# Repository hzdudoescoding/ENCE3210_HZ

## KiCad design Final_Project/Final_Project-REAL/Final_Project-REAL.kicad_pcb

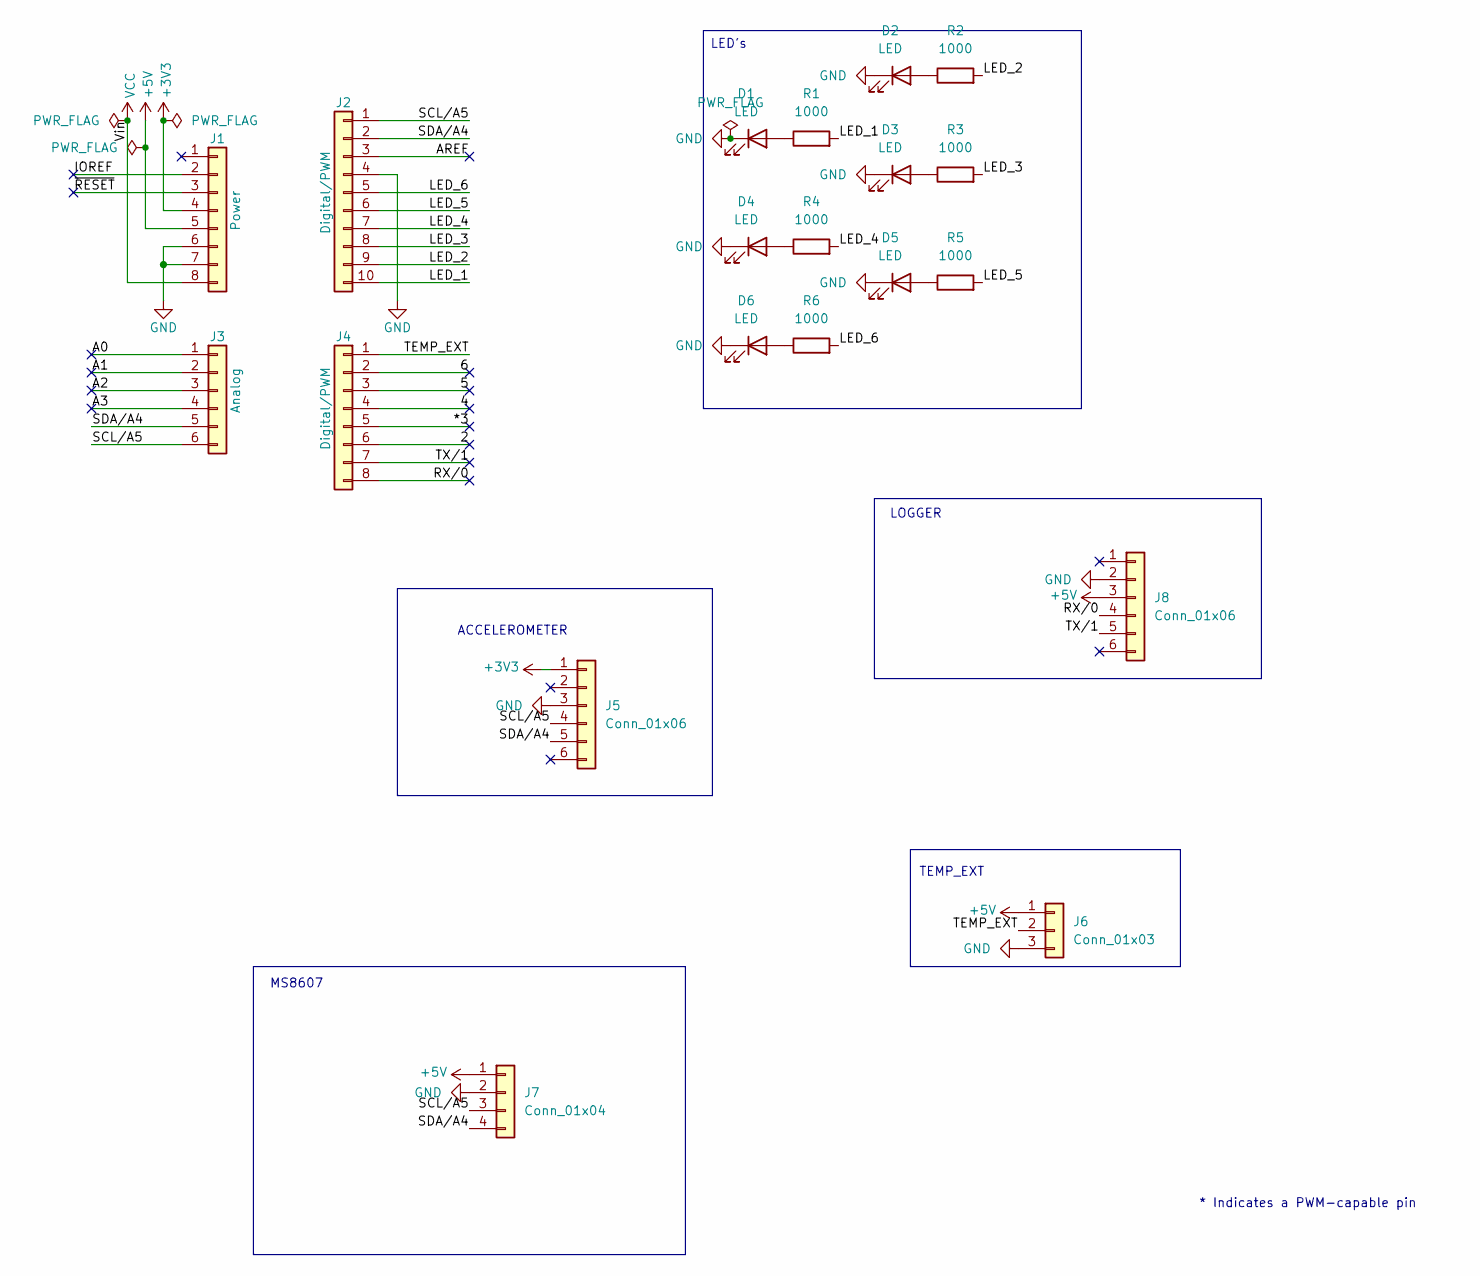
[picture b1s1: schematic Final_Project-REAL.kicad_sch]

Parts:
D1, D2, D3, D4, D5, D6: LED; LED_D5.0mm
J1: Power; PinSocket_1x08_P2.54mm_Vertical
J2: Digital/PWM; PinSocket_1x10_P2.54mm_Vertical
J3: Analog; PinSocket_1x06_P2.54mm_Vertical
J4: Digital/PWM; PinSocket_1x08_P2.54mm_Vertical
J5, J8: Conn_01x06; PinSocket_1x06_P2.54mm_Vertical
J6: Conn_01x03; JST_XH_B3B-XH-A_1x03_P2.50mm_Vertical
J7: Conn_01x04; PinSocket_1x04_P2.54mm_Vertical
R1, R2, R3, R4, R5, R6: 1000; R_Axial_DIN0207_L6.3mm_D2.5mm_P10.16mm_Horizontal

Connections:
+3V3: J1.4, J5.1
+5V: J1.5, J6.1, J7.1, J8.3
/2: J4.6
/4: J4.4
/5: J4.3
/6: J4.2
/*3: J4.5
/A0: J3.1
/A1: J3.2
/A2: J3.3
/A3: J3.4
/AREF: J2.3
/IOREF: J1.2
/LED_1: J2.10, R1.2
/LED_2: J2.9, R2.2
/LED_3: J2.8, R3.2
/LED_4: J2.7, R4.2
/LED_5: J2.6, R5.2
/LED_6: J2.5, R6.2
/RX/0: J4.8, J8.4
/SCL/A5: J2.1, J3.6, J5.4, J7.3
/SDA/A4: J2.2, J3.5, J5.5, J7.4
/TEMP_EXT: J4.1, J6.2
/TX/1: J4.7, J8.5
/~RESET: J1.3
GND: D1.1 (K), D2.1 (K), D3.1 (K), D4.1 (K), D5.1 (K), D6.1 (K), J1.6, J1.7, J2.4, J5.3, J6.3, J7.2, J8.2
unnamed: D1.2 (A), R1.1
unnamed: D2.2 (A), R2.1
unnamed: D3.2 (A), R3.1
unnamed: D4.2 (A), R4.1
unnamed: D5.2 (A), R5.1
unnamed: D6.2 (A), R6.1
VCC: J1.8

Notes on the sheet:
TEMP_EXT
MS8607
* Indicates a PWM-capable pin
LED's
LOGGER
ACCELEROMETER

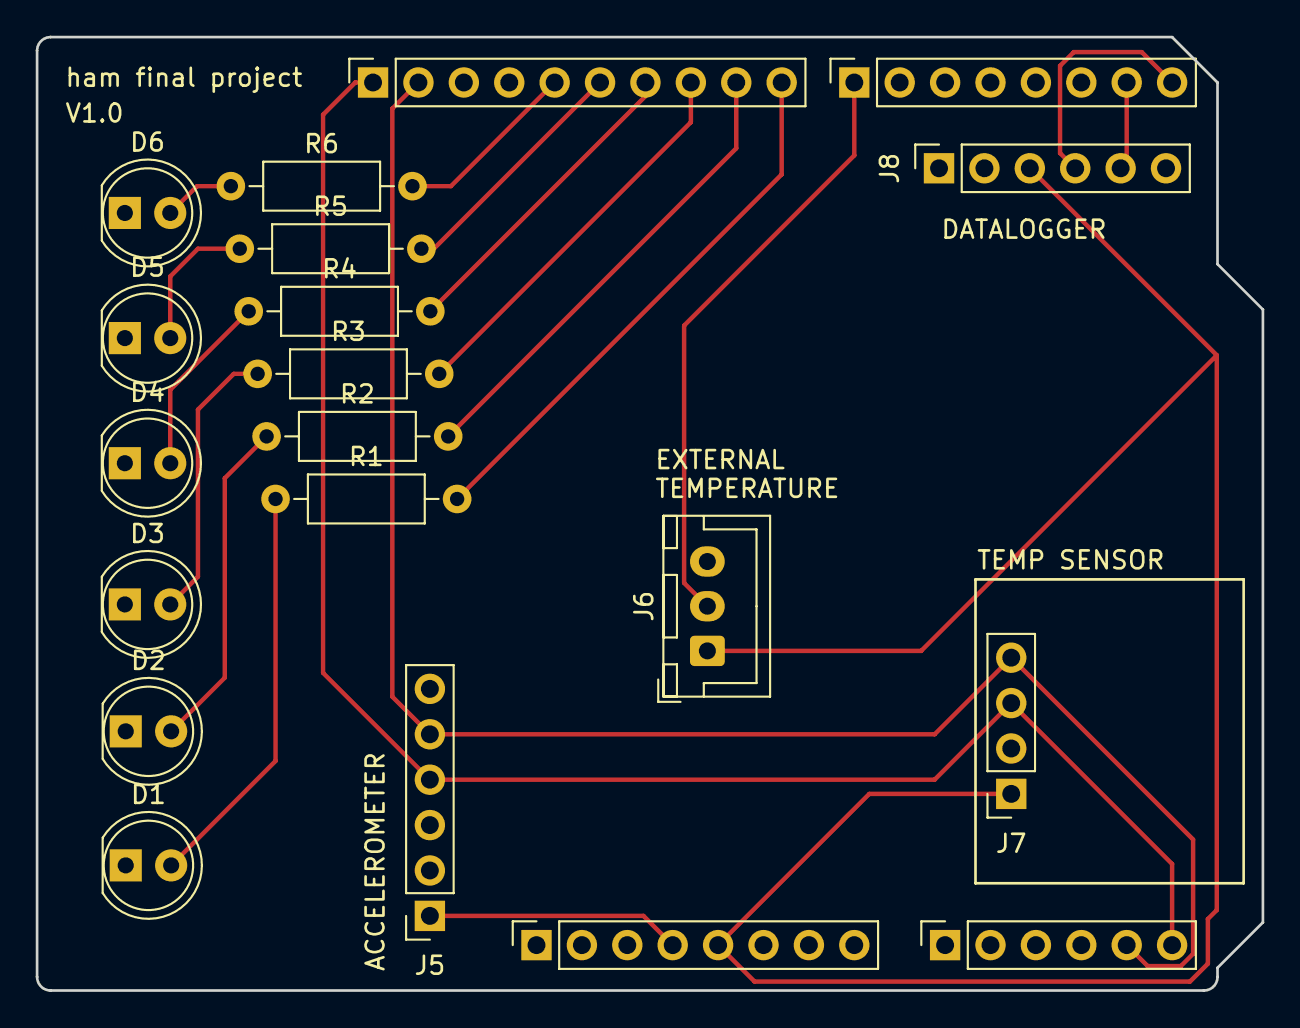
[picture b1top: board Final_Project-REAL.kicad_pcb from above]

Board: 2 copper layers, 68.6 x 53.3 mm, 20 parts (0 on the bottom side), 20 nets.

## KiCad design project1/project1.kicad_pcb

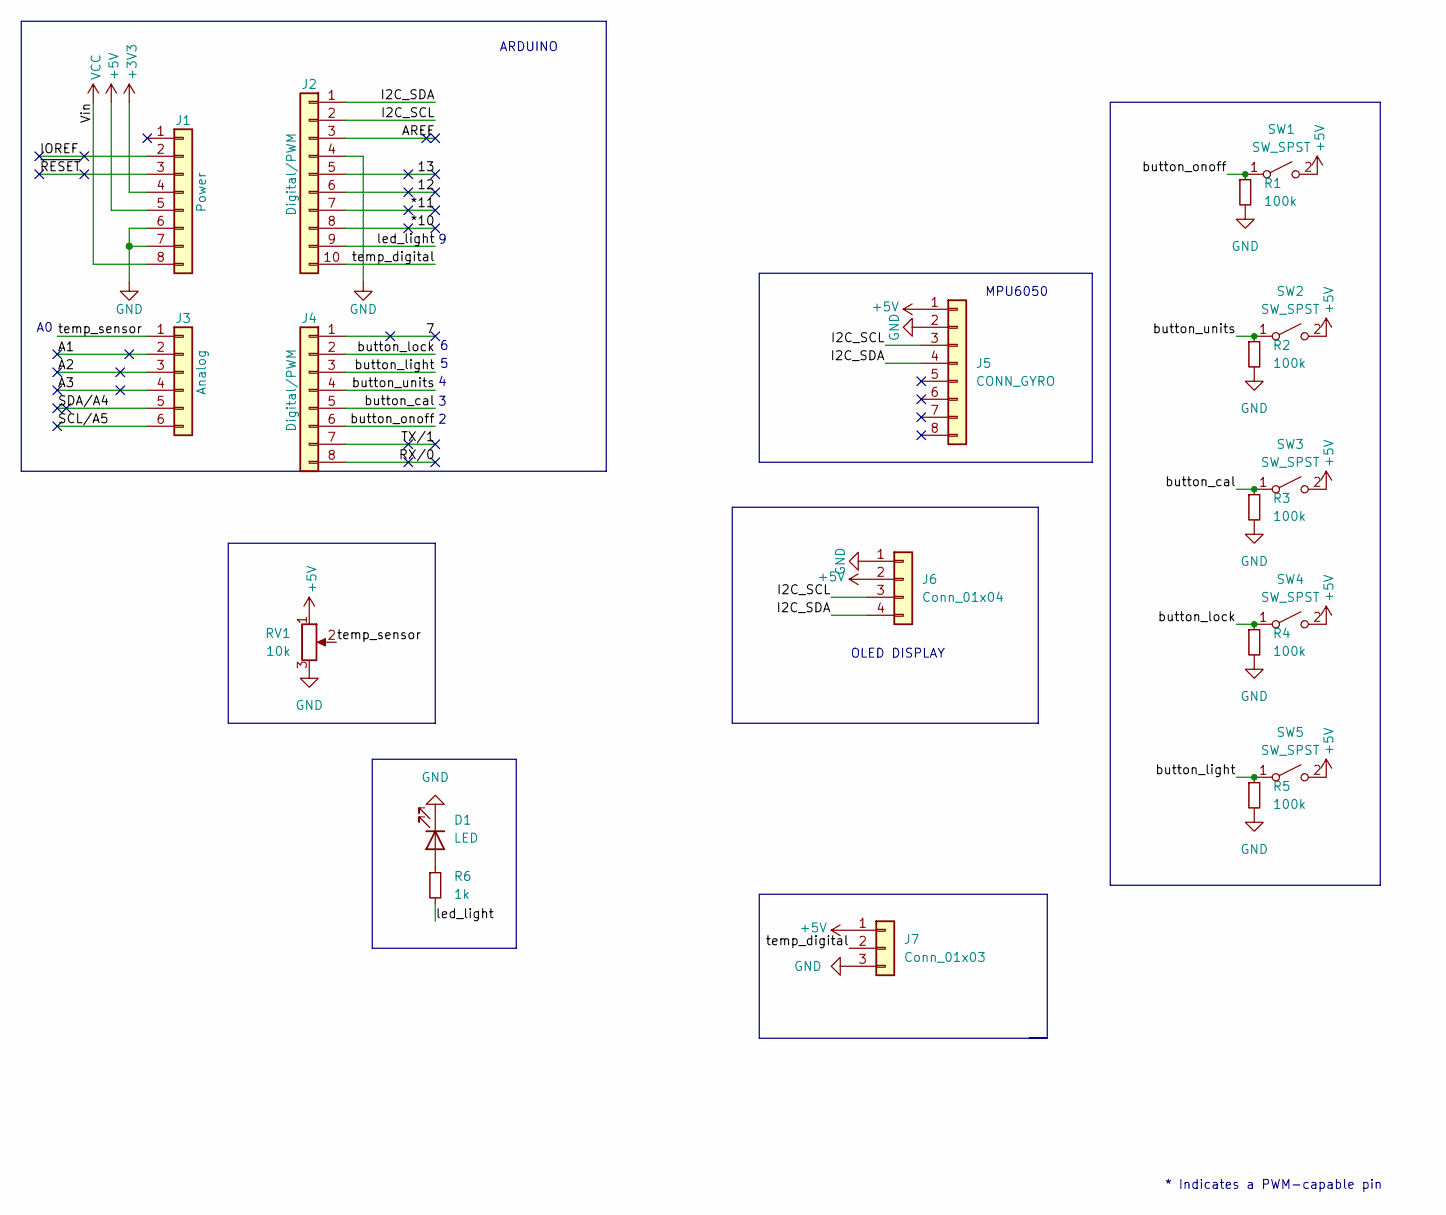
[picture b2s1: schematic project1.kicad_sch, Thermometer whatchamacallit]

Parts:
D1: LED; LED_D5.0mm
J1: Power; PinSocket_1x08_P2.54mm_Vertical
J2: Digital/PWM; PinSocket_1x10_P2.54mm_Vertical
J3: Analog; PinSocket_1x06_P2.54mm_Vertical
J4: Digital/PWM; PinSocket_1x08_P2.54mm_Vertical
J5: CONN_GYRO; PinSocket_1x08_P2.54mm_Vertical
J6: Conn_01x04; PinSocket_1x04_P2.54mm_Vertical
J7: Conn_01x03; JST_XH_B3B-XH-A_1x03_P2.50mm_Vertical
R1, R2, R3, R4, R5: 100k; R_Axial_DIN0207_L6.3mm_D2.5mm_P10.16mm_Horizontal
R6: 1k; R_Axial_DIN0207_L6.3mm_D2.5mm_P10.16mm_Horizontal
RV1: 10k; Potentiometer_Bourns_3386P_Vertical
SW1, SW2, SW3, SW4, SW5: SW_SPST; SW_PUSH_6mm

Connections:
+3V3: J1.4
+5V: J1.5, J5.1, J6.2, J7.1, RV1.1, SW1.2 (B), SW2.2 (B), SW3.2 (B), SW4.2 (B), SW5.2 (B)
/7: J4.1
/12: J2.6
/13: J2.5
/*10: J2.8
/*11: J2.7
/A1: J3.2
/A2: J3.3
/A3: J3.4
/AREF: J2.3
/I2C_SCL: J2.2, J5.3, J6.3
/I2C_SDA: J2.1, J5.4, J6.4
/IOREF: J1.2
/RX/0: J4.8
/SCL/A5: J3.6
/SDA/A4: J3.5
/TX/1: J4.7
/button_cal: J4.5, R3.1, SW3.1 (A)
/button_light: J4.3, R5.1, SW5.1 (A)
/button_lock: J4.2, R4.1, SW4.1 (A)
/button_onoff: J4.6, R1.1, SW1.1 (A)
/button_units: J4.4, R2.1, SW2.1 (A)
/led_light: J2.9, R6.2
/temp_digital: J2.10, J7.2
/temp_sensor: J3.1, RV1.2
/~RESET: J1.3
GND: D1.1 (K), J1.6, J1.7, J2.4, J5.2, J6.1, J7.3, R1.2, R2.2, R3.2, R4.2, R5.2, RV1.3
unnamed: D1.2 (A), R6.1
VCC: J1.8

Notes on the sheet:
OLED DISPLAY
ARDUINO
MPU6050
* Indicates a PWM-capable pin

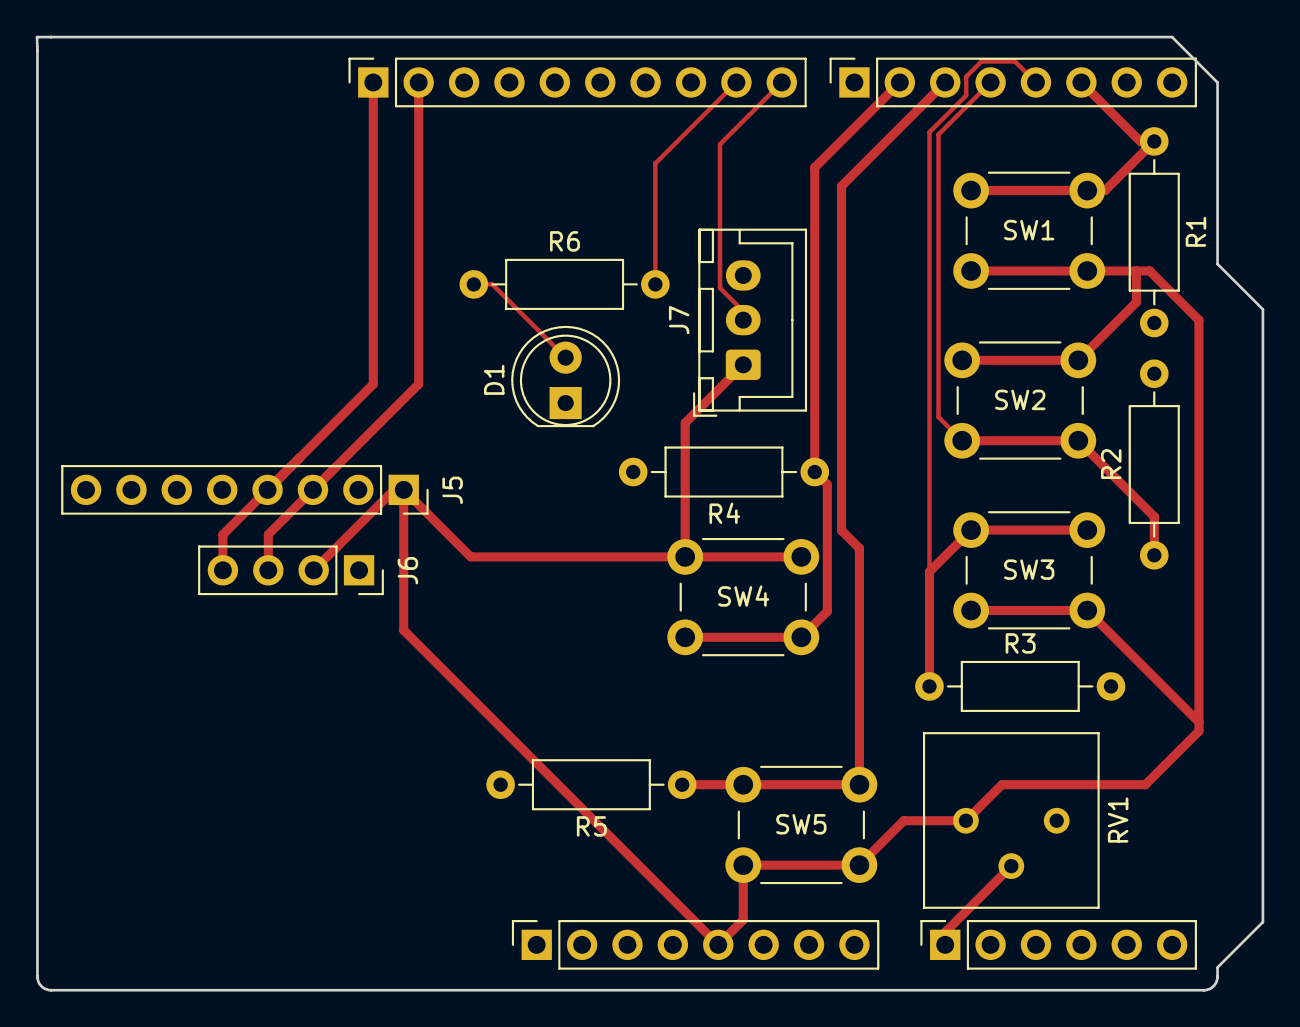
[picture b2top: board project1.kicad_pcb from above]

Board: 2 copper layers, 68.6 x 53.3 mm, 20 parts (0 on the bottom side), 13 nets.

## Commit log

2025-01-10 Create LAB1_Q2
2025-01-10 test
2025-01-17 lab1 completed
2025-01-17 lab1 done
2025-01-17 Create Lab1_Q1
2025-01-17 forgot how to make folder! will rework next lab :))))
2025-01-17 forgot how tortoise works
2025-01-24 Create Lab2_Q1
2025-01-31 Create Lab3Q1
2025-02-26 time for gaming!
2025-03-01 lab4 done
2025-03-14 FINALPROJECT COMPLETE
